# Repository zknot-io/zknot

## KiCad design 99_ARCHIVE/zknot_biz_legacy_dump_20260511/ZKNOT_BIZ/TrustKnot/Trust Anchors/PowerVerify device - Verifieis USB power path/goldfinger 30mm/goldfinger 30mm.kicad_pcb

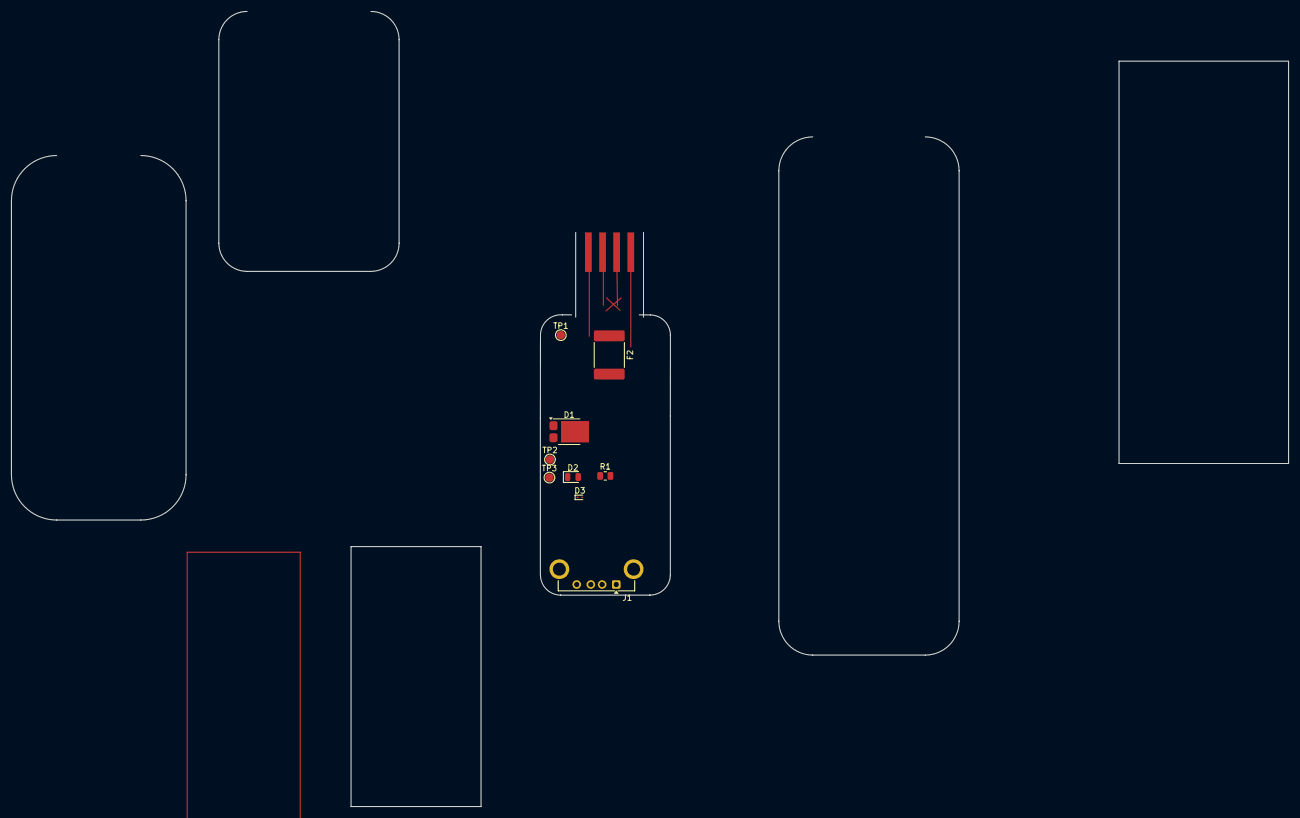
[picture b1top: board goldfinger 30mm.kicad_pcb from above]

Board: 2 copper layers, 9 parts (0 on the bottom side), 4 nets, no tracks yet.

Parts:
D1: PMEG030V050EPD; Nexperia_CFP15_SOT-1289
D2: LED_Small; LED_0805_2012Metric
D3: ESD9B5.0ST5G; D_SOD-923
F2: Polyfuse_Small; Fuse_2920_7451Metric
J1: USB_A; USB_A_Connfly_DS1095
R1: R_Small; R_0805_2012Metric
TP1, TP2, TP3: TestPoint; TestPoint_Pad_D1.5mm

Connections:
/VBUS_IN: F2.1, TP1.1
/VBUS_OUT: D1.3 (K), D3.2 (A2), J1.1 (VBUS), R1.1, TP2.1
GND: D1.1 (A), D1.2 (A), D2.2 (A), D3.1 (A1), F2.2, J1.4 (GND), J1.5 (Shield), TP3.1
unnamed: D2.1 (K), R1.2

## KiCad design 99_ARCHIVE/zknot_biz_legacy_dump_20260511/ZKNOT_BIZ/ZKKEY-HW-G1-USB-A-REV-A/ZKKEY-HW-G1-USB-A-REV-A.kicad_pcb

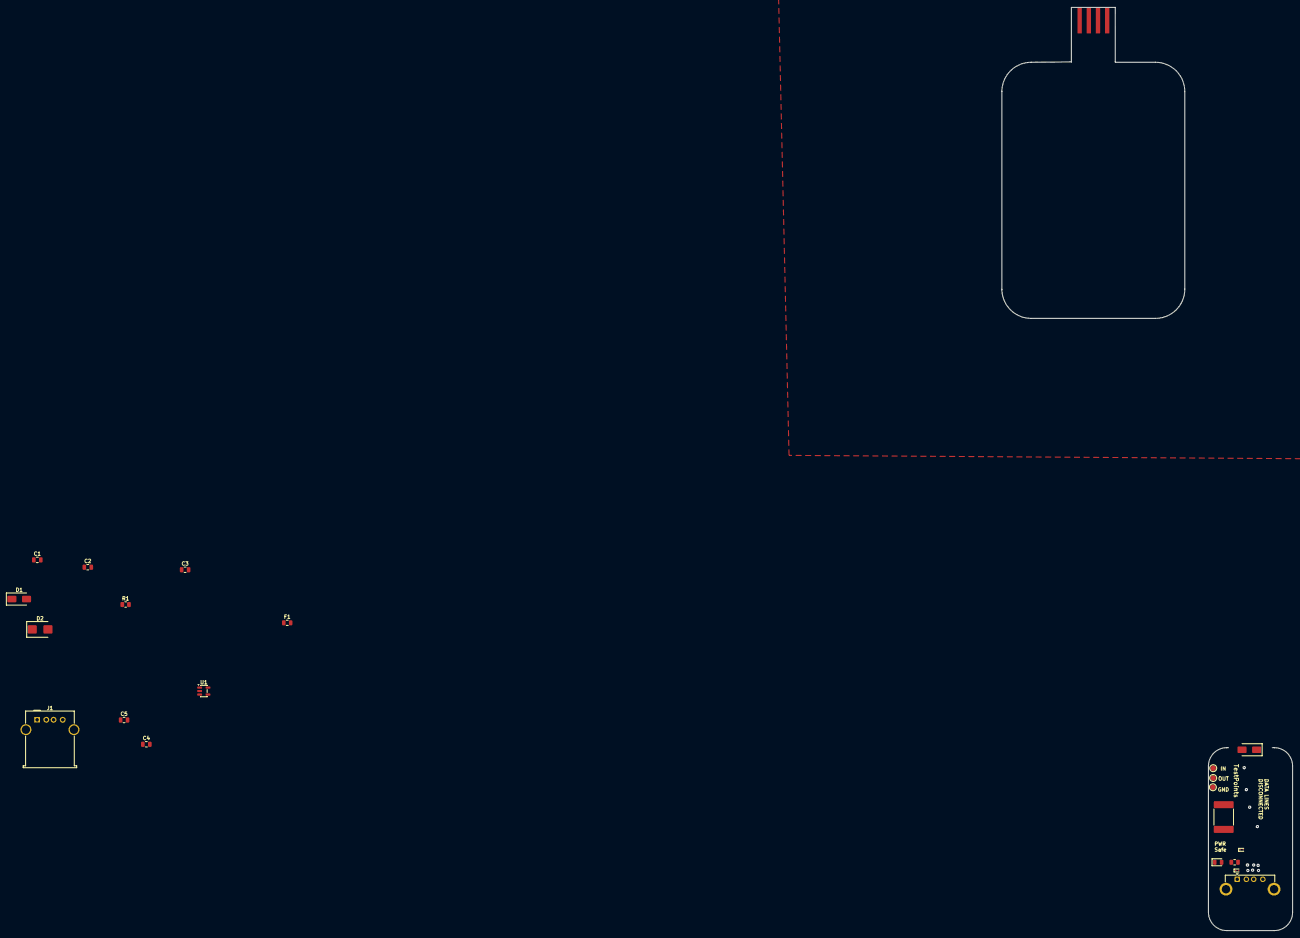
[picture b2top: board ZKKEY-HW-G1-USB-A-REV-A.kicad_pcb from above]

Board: 2 copper layers, 21 parts (0 on the bottom side), 13 nets, no tracks yet.

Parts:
C1: 4.7uF; C_0805_2012Metric
C2: .1uF; C_0805_2012Metric
C3: 1nF; C_0805_2012Metric
C4, C5: 1uF; C_0805_2012Metric
D1: SS54; D_SMA
D1#2, D3: ESD9B5.0ST5G; D_SOD-923
D2: LED_Small; LED_0805_2012Metric
D2#2: SM6T6V8A; D_SMB
D4: MBRA340; D_SMA
F1: Polyfuse; Fuse_2920_7451Metric
F1#2: Polyfuse; Fuse_0805_2012Metric
J1: USB_A; USB_A_Connfly_DS1095
J1#2: USB_A; USB_A_Molex_67643_Horizontal
R1: R_Small; R_0805_2012Metric
R1#2: 1M; R_0805_2012Metric
TP1, TP2, TP3: TestPoint; TestPoint_Pad_D1.5mm
U1: AP2112K-3.3; SOT-23-5

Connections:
/01_POWER_INPUT/USB_SHIELD: C3.1, J1#2.5 (Shield), R1#2.1
/02_REGULATION/+3V3: C4.1, C5.1, U1.1 (VIN), U1.3 (EN), U1.5 (VOUT)
/GND: D2.2 (A), D3.1 (A1), D4.1 (K), F1.2, J1.4 (GND), J1.5 (Shield), TP3.1
/VBUS_IN: D1#2.1 (A1), TP1.1
/VBUS_OUT: D3.2 (A2), D4.2 (A), J1.1 (VBUS), R1.1, TP2.1
unnamed: C1.1, C2.1
unnamed: D1#2.2 (A2), F1.1
unnamed: D1.1 (K), D2#2.2 (A2)
unnamed: D2#2.1 (A1), F1#2.2
unnamed: D2.1 (K), R1.2
unnamed: F1#2.1, J1#2.1 (VBUS)
unnamed: C4.2, C5.2, U1.2 (GND)
VBUS_RAW: C1.2, C2.2, C3.2, D1.2 (A), J1#2.4 (GND), R1#2.2

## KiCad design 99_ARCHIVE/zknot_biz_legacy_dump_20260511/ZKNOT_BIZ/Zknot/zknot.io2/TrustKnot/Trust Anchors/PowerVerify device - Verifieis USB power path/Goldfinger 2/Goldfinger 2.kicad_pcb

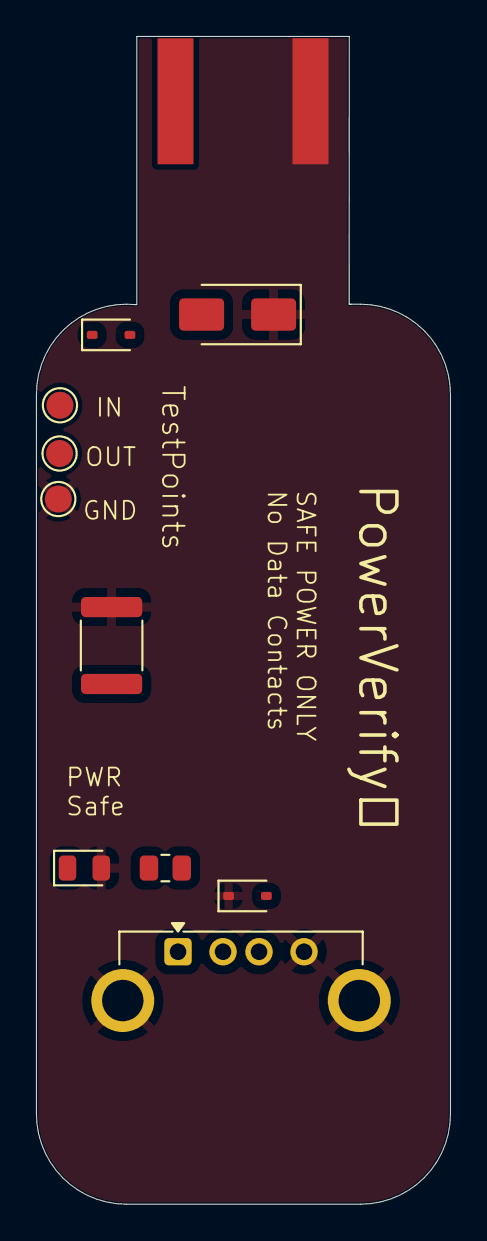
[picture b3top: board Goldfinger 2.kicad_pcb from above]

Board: 2 copper layers, 23.0 x 64.9 mm, 11 parts (0 on the bottom side), 5 nets, no tracks yet.

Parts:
D1, D3: ESD9B5.0ST5G; D_SOD-323
D2: LED_Small; LED_0805_2012Metric
D4: MBRA340; D_SMA
F1: Polyfuse; Fuse_1812_4532Metric
J1: USB_A; USB_A_Connfly_DS1095
J1#2: PowerVerify_PowerBlade; USB_A_PowerVerify_2Finger_2.4mm_FIXED
R1: R_Small; R_0805_2012Metric
TP1, TP2, TP3: TestPoint; TestPoint_Pad_D1.5mm

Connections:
/GND: D2.2 (A), D3.1 (A1), D4.1 (K), F1.2, J1.4 (GND), J1.5 (Shield), J1#2.2, TP3.1
/VBUS_IN: D1.1 (A1), J1#2.1, TP1.1
/VBUS_OUT: D3.2 (A2), D4.2 (A), J1.1 (VBUS), R1.1, TP2.1
unnamed: D1.2 (A2), F1.1
unnamed: D2.1 (K), R1.2

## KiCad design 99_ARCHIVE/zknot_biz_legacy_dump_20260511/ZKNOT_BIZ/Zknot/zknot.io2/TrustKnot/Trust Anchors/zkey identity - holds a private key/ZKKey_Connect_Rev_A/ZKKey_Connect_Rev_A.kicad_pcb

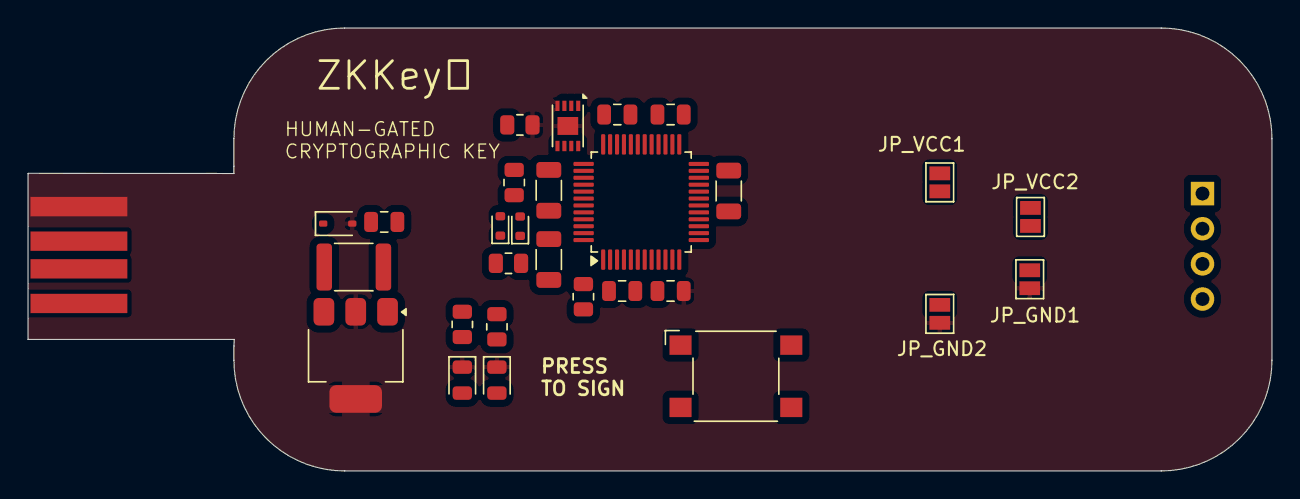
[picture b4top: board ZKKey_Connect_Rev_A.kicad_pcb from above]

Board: 2 copper layers, 89.9 x 32.0 mm, 30 parts (1 on the bottom side), 21 nets, no tracks yet.

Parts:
C1, C7, C8: 4.7-10uF; C_1206_3216Metric
C2, C3, C4, C5: .1uF; C_0805_2012Metric
C6: 100nF; C_0805_2012Metric
D1, D2: LED; LED_0805_2012Metric
D3: PTVS5V0Z1USK; D_SOD-323
D4, D5: ESD5Zxx; D_SOD-523
F1: Polyfuse; Fuse_1812_4532Metric
J1: USB_A_4Pin; USB_A_PowerVerify_4Pin_2.4mm
J2: Conn_01x04_Pin; PinHeader_1x04_P2.54mm_Horizontal
JP1: JP_VCC1; SolderJumper-2_P1.3mm_Open_Pad1.0x1.5mm
JP2: JP_VCC2; SolderJumper-2_P1.3mm_Open_Pad1.0x1.5mm
JP3: JP_GND1; SolderJumper-2_P1.3mm_Open_Pad1.0x1.5mm
JP4: JP_GND2; SolderJumper-2_P1.3mm_Open_Pad1.0x1.5mm
R1, R2: 330-1k; R_0805_2012Metric
R3: 10k; R_0805_2012Metric
R4: 100k; R_0805_2012Metric
R5, R6: 22; R_0805_2012Metric
SW1: SW_Push; SW_SPST_Omron_B3FS-100xP
U1: ATECC608A-MAHDA; DFN-8-1EP_3x2mm_P0.5mm_EP1.3x1.5mm
U2: STM32F103CBTx; LQFP-48_7x7mm_P0.5mm
U3: SPX2920M3-3.3_SOT223; SOT-223-3_TabPin2

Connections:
+3.3V: C1.1, C1.2, C2.1, C2.2, C3.1, C3.2, C4.1, C4.2, C5.1, C5.2, JP1.1 (A), JP2.1 (A), R3.1, SW1.2, U1.8 (VCC), U2.24 (VDD), U2.36 (VDD), U2.48 (VDD), U3.3 (VO)
/OLED_PIN1: J2.OLED_PIN1 (Pin_1), JP1.2 (B), JP2.2 (B)
/OLED_PIN2: J2.OLED_PIN2 (Pin_2), JP3.2 (B), JP4.2 (B)
/OLED_SCL: C7.1, C7.2, J2.OLED_SCL (Pin_3), U1.6 (SCL), U2.42 (PB6)
/OLED_SDA: C8.2, J2.OLED_SDA (Pin_4)
/USB_DM: D4.2 (A), J1.2
/USB_DP: D5.1 (K), J1.3, R5.2
/VBUS_FUSED: F1.2, U3.1 (VI)
/VBUS_RAW: D3.1 (K), F1.1, J1.1
GND: C6.2, D1.1 (K), D2.1 (K), D3.2 (A), J1.4, JP3.1 (A), JP4.1 (A), R4.2, U1.4 (GND), U1.9 (EP), U2.23 (VSS), U2.35 (VSS), U2.47 (VSS), U3.2 (GND)
unnamed: D1.2 (A), R1.2
unnamed: D2.2 (A), R2.2
unnamed: D4.1 (K), R6.2
unnamed: C8.1, U1.5 (SDA), U2.43 (PB7)
unnamed: R4.1, U2.44 (BOOT0)
unnamed: C6.1, R3.2, U2.7 (NRST)
unnamed: SW1.1, U2.10 (PA0)
unnamed: R1.1, U2.11 (PA1)
unnamed: R2.1, U2.12 (PA2)
unnamed: R5.1, U2.32 (PA11)
unnamed: R6.1, U2.33 (PA12)

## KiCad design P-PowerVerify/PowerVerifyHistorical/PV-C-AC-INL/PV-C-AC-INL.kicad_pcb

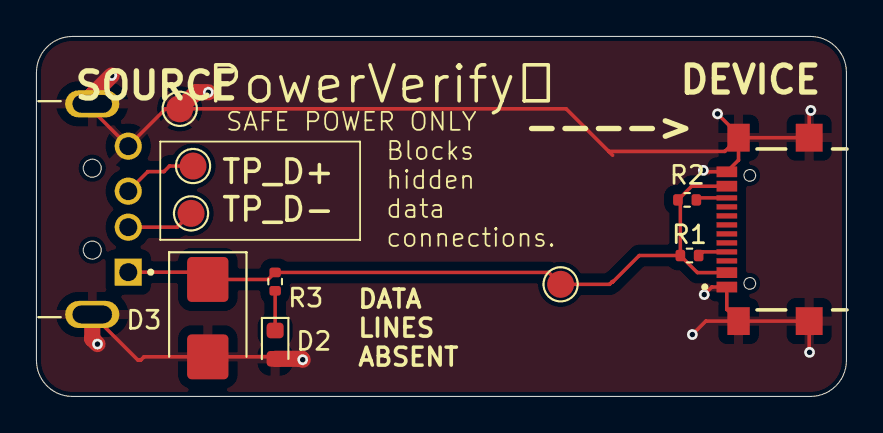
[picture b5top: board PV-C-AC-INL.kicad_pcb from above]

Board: 2 copper layers, 45.0 x 20.0 mm, 11 parts (0 on the bottom side), 7 nets.

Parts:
D2: LED; LED_0603_1608Metric
D3: SMBJ5.0A; D_SMB
J1: UP2-AH-1-TH; CUI_UP2-AH-1-TH
J2: USB4216-03-A_REVA; GCT_USB4216-03-A_REVA
R1, R2: 5.1K; R_0402_1005Metric
R3: 470ohm; R_0402_1005Metric
TP1, TP2, TP3, TP4: TestPoint; TestPoint_Pad_D1.5mm

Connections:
/GND: D2.2 (A), D3.2 (A2), J1.4 (GND), J1.SH1 (SHIELD), J1.SH2 (SHIELD), J2.A1_B12 (GND_A), J2.B1_A12 (GND_B), J2.SH1 (SHIELD), J2.SH2 (SHIELD), J2.SH3 (SHIELD), J2.SH4 (SHIELD), TP4.1
/LED: D2.1 (K), R3.1
/TP_DMINUS: J1.2 (D-), TP1.1
/TP_DPLUS: J1.3 (D+), TP2.1
/VBUS: D3.1 (A1), J1.1 (VCC), J2.A4_B9 (VBUS_A), J2.B4_A9 (VBUS_B), R1.1, R2.2, R3.2, TP3.1
unnamed: J2.A5 (CC1), R1.2
unnamed: J2.B5 (CC2), R2.1
